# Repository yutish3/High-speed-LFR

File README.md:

# LFR - 2026
STM32 line follower robot on a custom 2-layer PCB. Black Pill (STM32F411) as a brain, TB6612FNG motor driver, 16-channel ARC16 line sensor, MPU6050 , and 3S LiPo through a 5V buck converter.

## VISION
I wanted to make a LFR that will be really good for competitions and i didt wanted it to fail mid run or during travel so i decided to make a pcb for it

Main goals:
- everything on a single PCB: power, motor driver, sensor connector, IMU
- run straight from a 3S LiPo with a power switch
- battery voltage monitoring so the robot knows when the pack is getting low (used 2 resistors for it connected to blackpill)
- status LEDs, a RESET button and a SAVE button for calibration
- test points for power pins

## what makes it special (main components)

&#9679; STM32F411CEU6 (Black Pill) :- main microcontroller, 100 MHz Cortex-M4 with hardware FPU

&#9679; TB6612FNG :- dual H-bridge motor driver for two N20 gear motors

&#9679; ARC16 :- 16-channel IR line sensor array on a single 8-pin header

&#9679; MPU6050 :- 6-axis IMU for gyro-assisted turning and stabilisation

&#9679; 3S LiPo + buck converter :- 11.1V battery, with the 5V rail for the sensor and the MCU

&#9679; N20 600 RPM motors :- small, light and fast for the size

## Images

## Bill of Materials

| Component | Purpose | Qty | Cost (INR) | Distributor |
| --- | --- | --- | --- | --- |
| N20 12V 600 RPM motor | main motor | 4 | ₹916 | Online |
| 11.1V 850mAh 30C 3S LiPo Battery Pack | Main power | 1 | ₹1,159 | Online |
| ARC16 Line Sensor | 16-channel IR line sensor array | 1 | ₹1,499 | Online |
| N20 Wheels | wheels | 1 | ₹349 | Online |
| N20 Caster Ball Wheel | Third support point | 1 | ₹39 | Online |
| Push Button 6x6x5 (pack of 10) | RESET and SAVE buttons | 1 | ₹19 | Online |
| 100 uF 35V cap | VSW bulk decoupling | 2 | ₹24 | Online |
| 220 uF 25V cap | +5V bulk decoupling | 4 | ₹28 | Online |
| XT60 Female to Nylon T-Connector | Battery plug adapter | 1 | ₹131 | Online |
| XT60PW Male Connector | Battery connector | 1 | ₹70 | Online |
| Rocker Switch | Main power switch | 1 | ₹12 | Online |
| Black Pill (STM32F411CEU6) | Main microcontroller | 1 | - | Bought offline |
| TB6612FNG Motor Driver | Dual motor driver | 1 | - | Bought offline |
| MPU6050 Module | 6-axis IMU | 1 | - | Bought offline |
| 5V Buck Converter Module | Battery to 5V (BUCK1) | 1 | - | Bought offline |
| Custom PCB | PCB | 1 | 1500 | whypcb |

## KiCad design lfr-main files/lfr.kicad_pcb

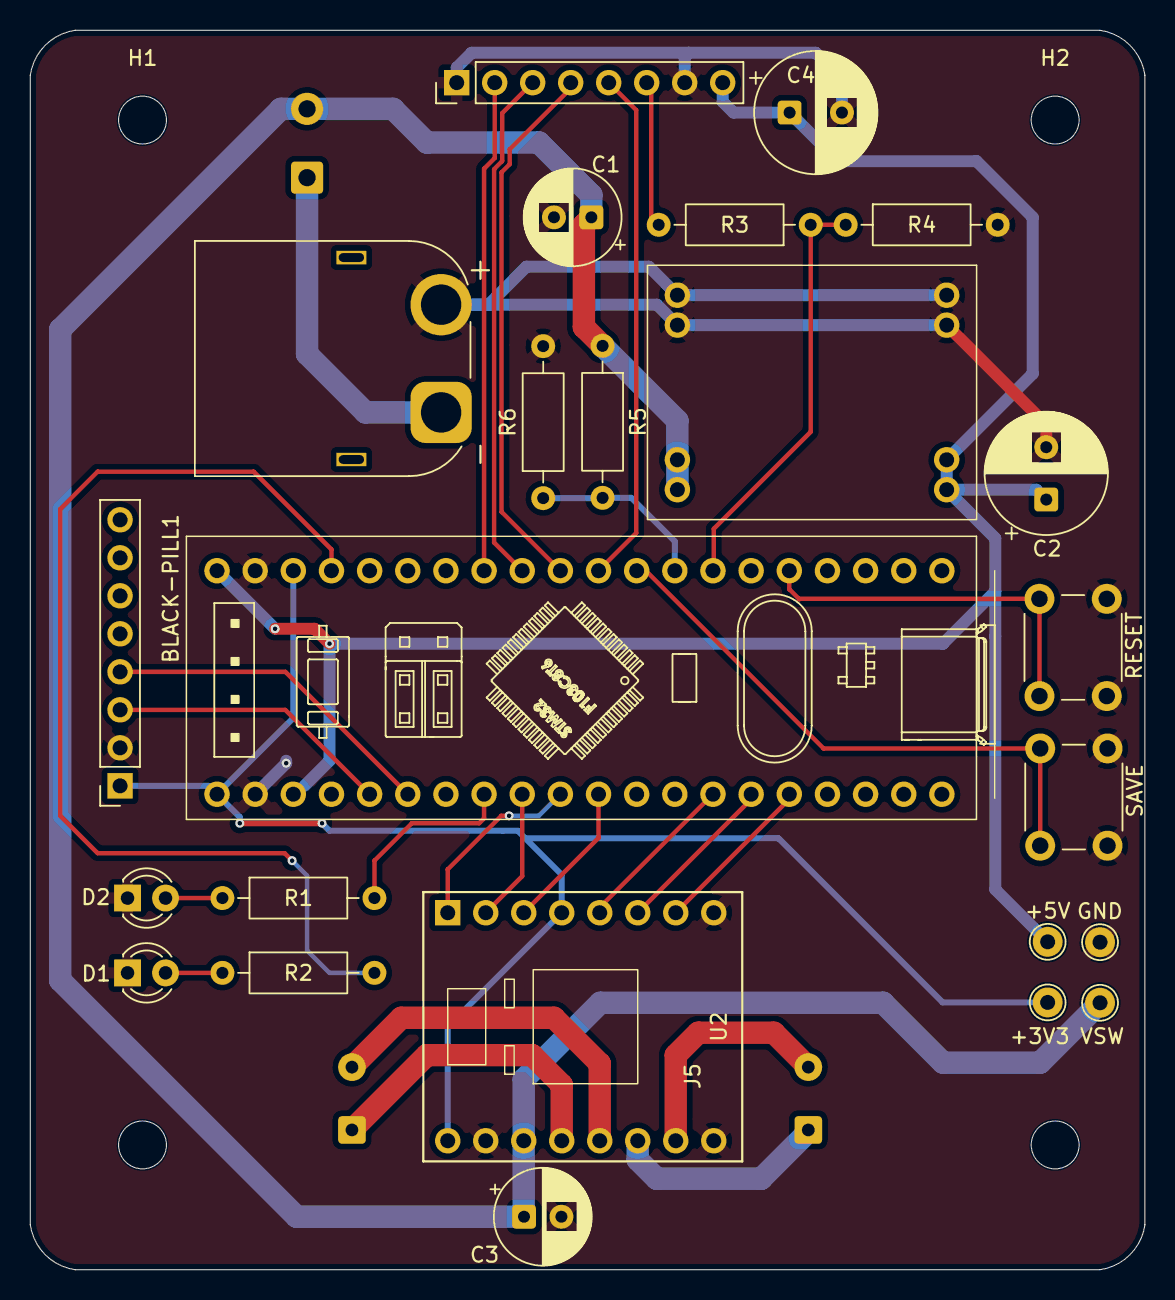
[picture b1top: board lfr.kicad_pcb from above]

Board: 2 copper layers, 74.5 x 82.8 mm, 31 parts (0 on the bottom side), 30 nets.

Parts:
+3V3: +3V3; TestPoint_THTPad_D2.0mm_Drill1.0mm
+5V: +5V; TestPoint_THTPad_D2.0mm_Drill1.0mm
BLACK-PILL1: BLACK PILL
BUCK1: Untitled_1
C1, C3: 100µF; CP_Radial_D6.3mm_P2.50mm
C2, C4: 220µF; CP_Radial_D8.0mm_P3.50mm
D1: GREEN; LED_D3.0mm
D2: RED; LED_D3.0mm
GND: GND; TestPoint_THTPad_D2.0mm_Drill1.0mm
H1, H2, H3, H4: MountingHole; MountingHole_3.2mm_M3
J1: Battery connector; AMASS_XT60PW-M_1x02_P7.20mm_Horizontal
J4: LEFT MOTOR; SolderWire-0.25sqmm_1x02_P4.2mm_D0.65mm_OD1.7mm
J5: RIGHT MOTOR; SolderWire-0.25sqmm_1x02_P4.2mm_D0.65mm_OD1.7mm
J7: LFS-16A sensor; PinHeader_1x08_P2.54mm_Vertical
J9: MPU6050; PinSocket_1x08_P2.54mm_Vertical
Jw2: SWITCH; SolderWire-0.5sqmm_1x02_P4.6mm_D0.9mm_OD2.1mm
R1, R2: 330Ω; R_Axial_DIN0207_L6.3mm_D2.5mm_P10.16mm_Horizontal
R3: 10k; R_Axial_DIN0207_L6.3mm_D2.5mm_P10.16mm_Horizontal
R4: 15k; R_Axial_DIN0207_L6.3mm_D2.5mm_P10.16mm_Horizontal
R5: 33k; R_Axial_DIN0207_L6.3mm_D2.5mm_P10.16mm_Horizontal
R6: 10K; R_Axial_DIN0207_L6.3mm_D2.5mm_P10.16mm_Horizontal
RESET: RESET; SW_PUSH_6mm
SAVE: SAVE; SW_PUSH_6mm
U2: TB6612FNG_Module; TB6612FNG_Breakout_2x07_P2.54mm
VSW: VSW; TestPoint_THTPad_D2.0mm_Drill1.0mm

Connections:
+3V3: +3V3.1 (1_1), BLACK-PILL1.18 (3V3), BLACK-PILL1.21 (3V3), J9.1 (VCC), U2.4 (STBY), U2.9 (VCC)
+5V: +5V.1 (1_1), BLACK-PILL1.20 (5V), BLACK-PILL1.23 (5V), BUCK1.3 (OUT+), BUCK1.4 (OUT+), C2.1, C4.1, J7.8 (5V)
A1: BLACK-PILL1.7 (A1), R3.1, R4.1
A01: J4.1 (LM1), U2.12 (AO1)
A2: BLACK-PILL1.8 (A2), R5.2, R6.1
A02: J4.2 (LM2), U2.13 (AO2)
A3: BLACK-PILL1.9 (A3), SAVE.1
A4: BLACK-PILL1.10 (A4), J7.5 (S0)
A5: BLACK-PILL1.11 (A5), J7.4 (S1)
A6: BLACK-PILL1.12 (A6), J7.3 (S2)
A7: BLACK-PILL1.13 (A7), J7.2 (S3)
B1: BLACK-PILL1.36 (A8), U2.7 (PWMB)
B01: J5.1 (RM1), U2.14 (BO2)
B02: J5.2 (RM2), U2.15 (BO1)
B3: BLACK-PILL1.30 (B3), U2.1 (PWMA)
B6: BLACK-PILL1.25 (B8), J9.3 (SCL)
B7: BLACK-PILL1.26 (B7), J9.4 (SDA)
B10: BLACK-PILL1.17 (B10), R2.2
B12: BLACK-PILL1.31 (A15), U2.3 (AIN1)
B13: BLACK-PILL1.29 (B4), U2.2 (AIN2)
B14: BLACK-PILL1.34 (A10), U2.5 (BIN1)
B15: BLACK-PILL1.35 (A9), U2.6 (BIN2)
GND: BLACK-PILL1.19 (GND), BLACK-PILL1.22 (GND), BUCK1.1 (OUT-), BUCK1.2 (OUT-), BUCK1.5 (IN-), BUCK1.6 (IN-), C1.2, C2.2, C3.2, C4.2, D1.1 (K), D2.1 (K), GND.1 (1_1), J1.2 (-), J7.1 (E), J7.7 (GND), J9.2 (GND), R4.2, R6.2, RESET.2, SAVE.2, U2.8 (GND), U2.10 (GND), U2.16 (GND)
unnamed: BLACK-PILL1.28 (B5), R1.2
unnamed: D1.2 (A), R2.1
unnamed: D2.2 (A), R1.1
unnamed: J7.6 (SIG), R3.2
R: BLACK-PILL1.5 (R), RESET.1
VBAT: J1.1 (+), Jw2.1 (S1)
VSW: BUCK1.7 (IN+), BUCK1.8 (IN+), C1.1, C3.1, Jw2.2 (S2), R5.1, U2.11 (VM), VSW.1 (1_1)
